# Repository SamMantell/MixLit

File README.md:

# MixLit - Work in Progress

The MixLit is a small sound desk that can control app volumes on a Windows PC. It uses an arduino nano as the controller and talks to our software over USB serial.

The case can be 3D printed and both STEP and STL files are provided

The PCB was designed in KiCAD and we used PCB Way to get them manafactured

Software is a Flutter application.

This repo contains firmware, software and hardware.

# Images
Image of the device:

PCB:

Software:

# 📦 Hardware
**» Order the Hardware we used from the links below.**

💡 WS2812B - LIGHTING - https://www.amazon.co.uk/dp/B0CF57NMHN

🎚️ 10K Ohm Slide Potentiometer - https://www.amazon.co.uk/dp/B07PNDLKQQ?psc=1

🎛️ 10K Ohm Rotation Potentiometer - https://www.amazon.co.uk/dp/B07B64MWRF?psc=1

🎮 Arduino Nano - https://www.amazon.co.uk/dp/B0CJHMZZWS

#

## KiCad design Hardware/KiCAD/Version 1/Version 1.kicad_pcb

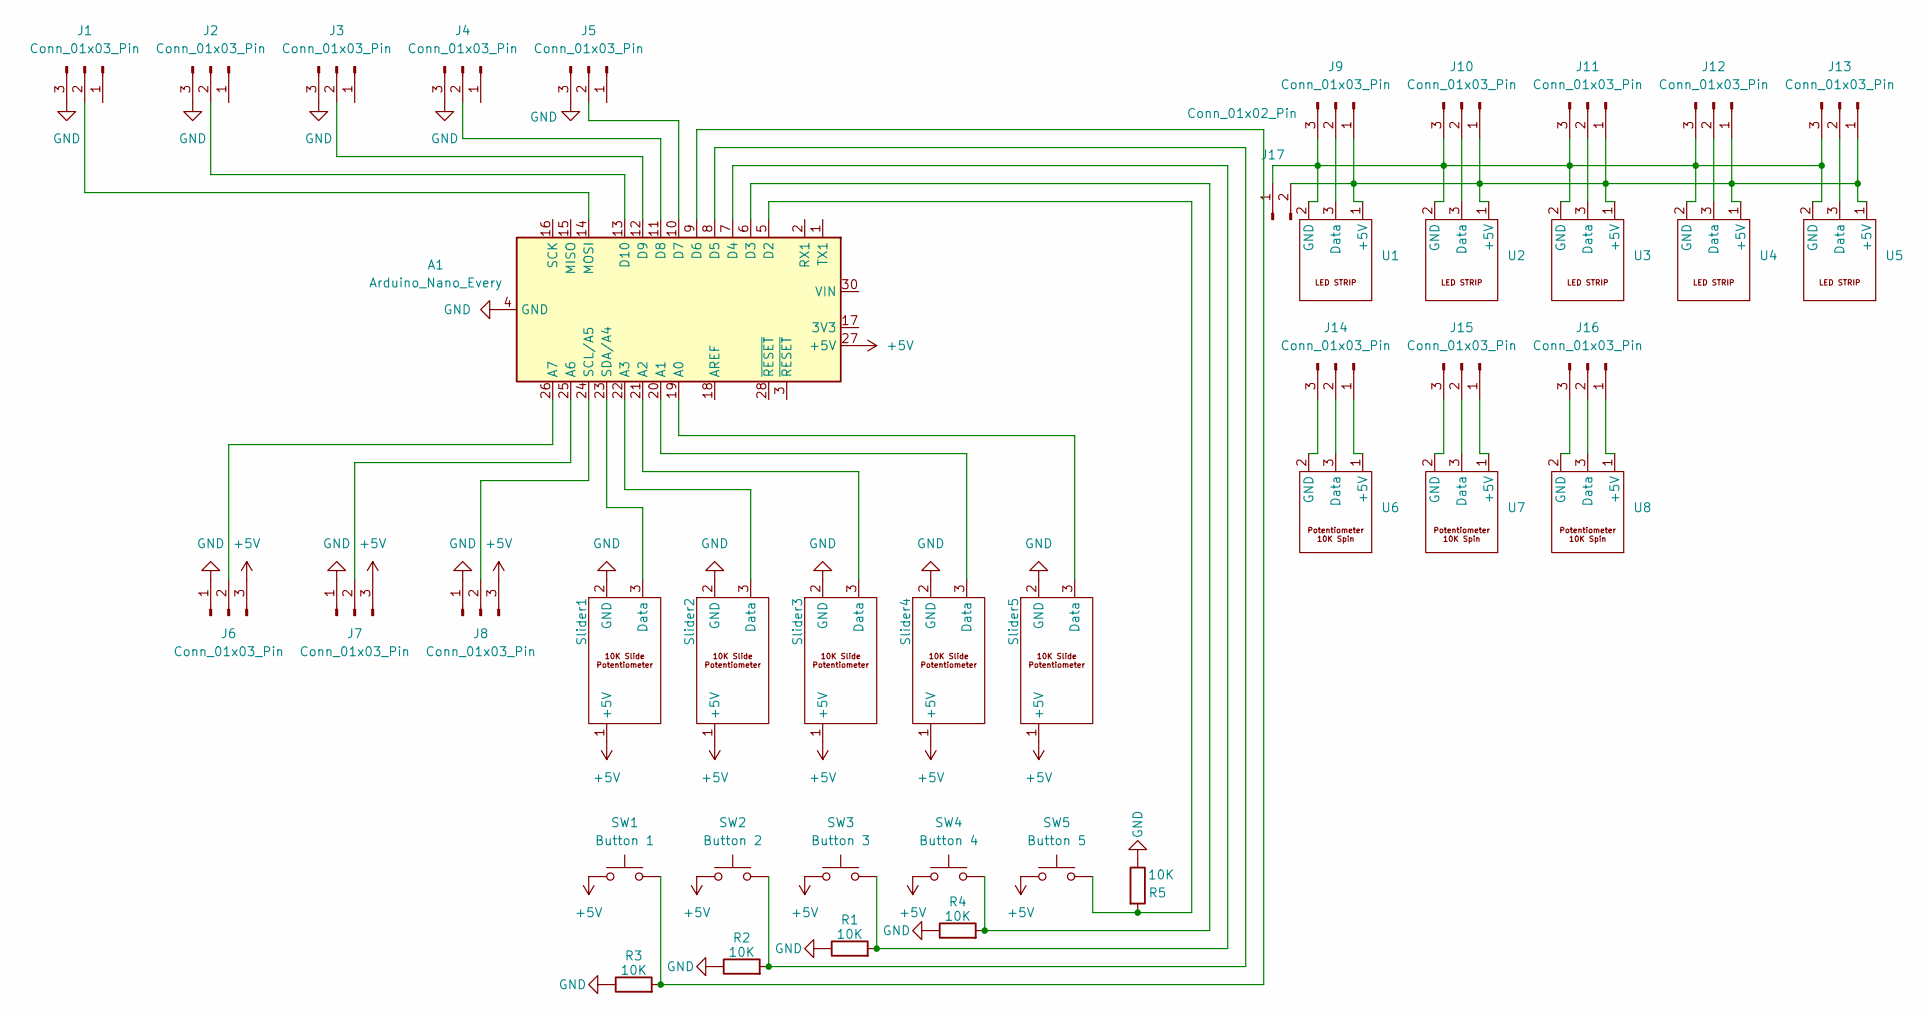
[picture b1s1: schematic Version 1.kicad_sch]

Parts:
A1: Arduino_Nano_Every; Arduino_Nano
J1, J2, J3, J4, J5, J6, J7, J8, J9, J10, J11, J12, J13, J14, J15, J16: Conn_01x03_Pin; PinHeader_1x03_P2.54mm_Vertical
J17: Conn_01x02_Pin; PinHeader_1x02_P2.54mm_Vertical
R1, R2, R3, R4, R5: 10K; R_Axial_DIN0204_L3.6mm_D1.6mm_P7.62mm_Horizontal
SW1: Button 1; SW_Cherry_MX_1.00u_PCB
SW2: Button 2; SW_Cherry_MX_1.00u_PCB
SW3: Button 3; SW_Cherry_MX_1.00u_PCB
SW4: Button 4; SW_Cherry_MX_1.00u_PCB
SW5: Button 5; SW_Cherry_MX_1.00u_PCB
Slider1, Slider2, Slider3, Slider4, Slider5: Custom Slide Potentiometer Double Linear 10K
U1, U2, U3, U4, U5: Custom LED Strip
U6, U7, U8: Custom Spin Potentiometer

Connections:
+5V: A1.27 (+5V), J6.3, J7.3, J8.3, SW1.1, SW2.1, SW3.1, SW4.1, SW5.1, Slider1.1 (+5V), Slider2.1 (+5V), Slider3.1 (+5V), Slider4.1 (+5V), Slider5.1 (+5V)
GND: A1.4 (GND), A1.29 (GND), J1.3, J2.3, J3.3, J4.3, J5.3, J6.1, J7.1, J8.1, R1.1, R2.1, R3.1, R4.1, R5.1, Slider1.2 (GND), Slider2.2 (GND), Slider3.2 (GND), Slider4.2 (GND), Slider5.2 (GND)
unnamed: A1.19 (A0), Slider5.3 (Data)
unnamed: A1.20 (A1), Slider4.3 (Data)
unnamed: A1.21 (A2), Slider3.3 (Data)
unnamed: A1.22 (A3), Slider2.3 (Data)
unnamed: A1.25 (A6), J7.2
unnamed: A1.26 (A7), J6.2
unnamed: A1.5 (D2), R5.2, SW5.2
unnamed: A1.6 (D3), R4.2, SW4.2
unnamed: A1.7 (D4), R1.2, SW3.2
unnamed: A1.8 (D5), R2.2, SW2.2
unnamed: A1.9 (D6), R3.2, SW1.2
unnamed: A1.10 (D7), J5.2
unnamed: A1.11 (D8), J4.2
unnamed: A1.12 (D9), J3.2
unnamed: A1.13 (D10), J2.2
unnamed: A1.14 (MOSI), J1.2
unnamed: A1.24 (SCL/A5), J8.2
unnamed: A1.23 (SDA/A4), Slider1.3 (Data)
unnamed: J9.2, U1.3 (Data)
unnamed: J9.1, J10.1, J11.1, J12.1, J13.1, J17.2, U1.1 (+5V), U2.1 (+5V), U3.1 (+5V), U4.1 (+5V), U5.1 (+5V)
unnamed: J10.2, U2.3 (Data)
unnamed: J9.3, J10.3, J11.3, J12.3, J13.3, J17.1, U1.2 (GND), U2.2 (GND), U3.2 (GND), U4.2 (GND), U5.2 (GND)
unnamed: J11.2, U3.3 (Data)
unnamed: J12.2, U4.3 (Data)
unnamed: J13.2, U5.3 (Data)
unnamed: J14.1, U6.1 (+5V)
unnamed: J14.2, U6.3 (Data)
unnamed: J14.3, U6.2 (GND)
unnamed: J15.1, U7.1 (+5V)
unnamed: J15.2, U7.3 (Data)
unnamed: J15.3, U7.2 (GND)
unnamed: J16.1, U8.1 (+5V)
unnamed: J16.2, U8.3 (Data)
unnamed: J16.3, U8.2 (GND)

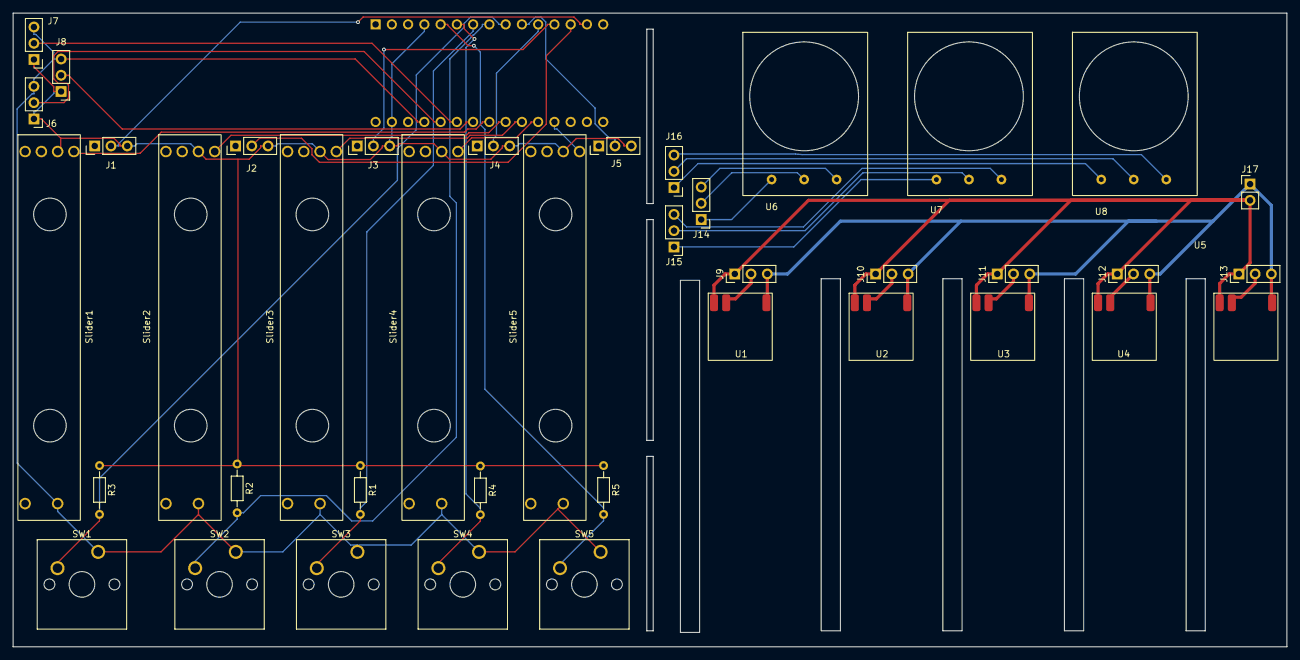
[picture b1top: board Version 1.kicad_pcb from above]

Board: 2 copper layers, 199.0 x 99.0 mm, 41 parts (1 on the bottom side), 36 nets.

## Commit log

2023-08-09 Update MixLit.ino
    Cleaned the code a little
2023-08-10 Optimised + 3D
    Code has been optimised and 3D document added
2023-08-10 Update README.md
    Added Links to Hardware Used
2023-08-10 Update README.md
    new lines are <br />???
2023-08-10 Working LEDS!!!
2023-08-10 bugs FIXED
2023-08-10 Now has Variable at top for deej or not
    woooooo
2023-08-10 test
2023-08-10 software
2023-08-10 clean main repository
2023-08-10 vs gone
2023-08-10 spotify slider test works
2023-08-10 Working-ish app selector for slider 1
2023-08-11 5 workin' slideroos
2023-08-11 quick spring cleaning
2023-08-11 Optimised LEDs
2023-08-12 ui fix
2023-08-14 UI design implementations
2023-08-14 Animation fixes
2023-08-14 attempting to fix sliders mk1
2023-08-14 mkII
2023-08-14 Close button
2023-08-15 might've screwed this optimistic experiment up but hopefully its cool
2023-08-15 some improvments and optimisations?
2023-08-16 Update
    Now 8 Sliders and MIDI usb commented out
2023-08-30 Working for MIDI
    Working now for MIDI VoiceMeter control using 5 sliders
2023-08-30 number wrong lol
2023-08-30 DATA stream lol
2023-09-01 Added some math to calculate values for voice meter
2024-01-05 MixLit V2 Added
    Added new library for the LEDs, now stored in a 2D array, Serial output optimised, some more general optimisations.
2024-01-08 Add Colours to LEDs
    Changed the `setLEDs()` function to make brightness easier and allows for use of colour pallets. Need to create custom colour pallets still.
2024-01-08 Made Cool Blue Colours
    Also some optimisations here and there
2024-01-09 Added Midi
    Can Now Control Voicemeter!!!
2024-01-10 Added a custom ColourPalette
    Added a Custom ColorPalette, do note in future a 16 byte colour palette will be needed to control the master slider while another 32 byte one will be used to control the other 4.
2024-01-11 Implementation of 2 ColorPalettes
    in theory this should add a colour palette for the main slider and one for the others allowing for potential individual addressment of the LEDs over software, wrote this on a coach, code not varified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
2024-01-12 Fixed code from yesterday
    Yeah that code didn't work, hopefully this should, actually verified this one and it should work, can't actually test it, also its not optimised at all atm.
2024-01-25 All White Colour Pallet
    Workin!
2024-01-25 Individually Addressable
    Made it possible to address each led individually with use of 2 arrays, one to control the main slider and the other to control the other 4. Fully Working!
2024-01-27 Remove Serial Communication
    (not using it for now and Arduino will wait for a connection in current config so removed.)
2024-02-01 Removed unnecessary Variables
2024-02-05 Update Non-Colourful
2024-02-07 Update To New Palettes
    No longer CONST!
2024-02-08 Neaten Code
2024-02-08 Update LED type
2024-02-12 Update to New Version
2024-02-12 Fix no `FastLED.show();` lol
2024-02-15 Optimisations
2024-02-15 comment out optimisation checks
2024-02-16 Combined Firmware Together
    Firmware now supports many different modes with a number of variables to enable / disable them.
2024-02-16 Start to read serial data
    tmp, kinda starting to work
2024-02-17 Progress to serial input
    It now takes input!!!
2024-02-17 Bit more progress to serial coms
2024-02-18 Working Serial Communication
    It do be working
2024-02-18 Re-organise code
2024-02-20 Some Documentation
2024-02-25 Remove unnecessary variables
2024-02-26 Few more comments
2024-04-19 Add MixLitLite
2024-05-10 Add first STLs
2024-11-13 add delay between updates
2024-11-13 voicemeter mode
2024-11-13 string build change
2024-11-14 decrease chance of noise
2024-11-14 2024 :)
2024-11-15 never back down never what 🗣️
2024-11-16 herm
2024-12-04 add blender referance
2024-12-04 pcb start
2024-12-05 some more pcbing
2024-12-06 pcb progress
2024-12-09 some more KiCAD Stuff
2024-12-11 more kicad stuff
2024-12-11 ready to order maybe
2024-12-11 to be ordererd
2024-12-20 some changes
2024-12-22 push...
2024-12-22 test one
2024-12-22 This works! Sliders and Pots only though
2024-12-22 Fully working except buttons
2024-12-22 🗣️🔥init 🍵🫖
2024-12-22 🔘🔳 button support maybe
2024-12-23 ✨feat: easily callable dialog for warning messages 🛠️fix: hang on failure of device detection/com-port-open (works with/without device connection now 🎉)
2024-12-23 add a wait for software connection
2024-12-23 ✨feat: device connection / disconnection listeners + toast notification
2024-12-23 fix brightness
2024-12-24 🛠️fix: device connect / disconnection listener
2024-12-24 fix leds going to zero
2024-12-24 ✨feat: mixlit device establishment via COM port call/response scanning ⚠️issues: non-immediate connection, last com port not stored, takes ages to find device, values aren't restored from device on i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
2024-12-24 🔥opt: sped up device recognition process
2024-12-24 🛠️fix: device + app volumes can now co-exist
2024-12-24 🛠️fix: weird ass muting bug
2024-12-28 🛠️fix: device scanning & detection
2025-01-02 add CLion version
2025-02-07 ermmmmm
2025-02-07 create v2
2025-02-07 add case v2
2025-02-16 add spin dial cover
2025-02-23 🛠️fix: basically everything
2025-02-23 ✨﻿ firmware now sends data after connection
    committing firmware to software
2025-02-24 optimise and add loading animation
2025-02-27 remove Clion Version
2025-02-27 remove clio metadata
2025-02-27 ✨ add loading animation
2025-02-27 Revert "Delete pubspec.lock"
    This reverts commit d0521a3f248a7181f752d74ffe61f75d296f536d.
2025-02-27 🔨Optimisations
2025-02-27 add assets
2025-05-09 🛠️ load last saved
2025-05-09 🛠️ Delay fix (fixes laggy result in software) - 50ms -> 10ms
2025-05-09 firmware
2025-05-09 🛠️ Windows volume lags when adjusting too often
2025-05-09 🛠️ Firmware: Reduced noise 🛠️ Prevented app being constantly assigned when volume adjustments are being made
2025-05-09 noise fixes
2025-05-10 ✨ Mute buttons
2025-05-10 🛠️ Mute buttons more responsive
2025-05-10 🧶Refactor: organised assets
2025-05-10 ✨ Basic UI Redesign
2025-05-10 ✨ feat: Saving to config for state restoration 🚢 prgrs: Device LED control from software 🧹 chore: updated logo and theme
2025-05-10 🛠️ Fix: inconsistent design, consistent font, better text clarity/translations
2025-05-10 🔧 tweak: updated app icon
2025-05-10 🛠️ fix: used local directory of application for config instead of documents 🧶ref: changed mixlit.yml to data.yml
2025-05-10 ✨ feat: (Auto) Updater ✨ feat: installer executable using inno 📂 file: added icons, and other assets required for this release
2025-05-10 🧹chore: organise graphic assets
2025-05-10 ✨ feat: Minimise to system tray
2025-05-10 🧹chore: versioning oopsie lol
2025-05-15 🧶 Refactor: finals/consts added where necessary
2025-05-15 ✨ feat: rate limiting for performance, caching 🧶 refactor: icon colour extraction, only using state when necessary 🔧 tweak: edited main.cpp for window size & title 🛠️ fix: firmware type errors
2025-05-15 colour change over serial
2025-05-15 🗣️init
2025-05-15 psuh
2025-05-16 ✨feat: better disconnection handling (no keepalive needed) 🛠️fix: prevented system apps (explorer.exe) without readable file path from causing slider assignment menu breaking ❌rm: temporarily removed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
2025-05-25 beginning to work with classes
2025-05-25 serial reader working with 1 command
2025-05-25 pre datasetled re-write
2025-05-25 working with new serial reader :)
2025-05-25 🔧updated baud rate to match firmware
2025-05-25 organised (almost)
2025-05-26 new code organised
2025-06-08 add buttons to firmware
2025-06-13 ✨ Launch (minimised) on startup ✨ Draggable window ✨ Slight app assigner menu UI update 🔧 Already assigned apps are not listed in app assigner 🛠️ Fixed device volume being muted on start
2025-06-26 support 2 potentiometers and colour gradients
2025-07-03 🛠️ fix #15: config now stored in appdata
2025-07-03 🛠️ fix: connection status indicator overflow (when disconnected)
2025-07-03 improve serial connection
2025-07-03 make only 2 dials for starts of dial integration (left one broke lol)
2025-07-03 ✨feat: dynamic audio session management & app caching (fixes #14)
2025-07-03 🛠️fix #18: show window on manual open (and minimise on startup)
2025-07-03 send all slider values even if 0
2025-07-03 LED updates are now instant
2025-07-07 ✨feat #20: dial support ✨feat #22: settings menu added 🛠️fix #23: mute buttons work again 🛠️fix #19: assigned apps no longer muted on launch
2025-07-07 🧶update version
2025-07-14 Feature - App Grouping
2025-07-17 STM32 moment
2025-10-11 ✨feat #16 - App Grouping ✨feat - Active application support ✨⚡feat+perf: API-based volume adjustment via Windows Service ❌rm: direct audio control
2025-10-30 🛠️ pre-tweaks
2025-10-31 ✨ feat: dynamic/live-updating app list (fixes #26) 🛠️ fix: app re-discovery works (and sets volume upon rediscovery if appropriate slider adjusted) 🛠️ fix #25: hardware values are properly restored u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
2025-11-23 ✨ added session caching 🛠️ fixed memory leak issues
2025-12-21 ✨ added integrations/plugins
2025-12-22 add !
2026-04-05 ✨ ----- VERSION 2.0.0 ----- ⚡ Moved all serial code to be handled by service instead 🛠️ Fixed new apps added to groups not instantly applying once saving the group changes (#28) ✨ Noise reduction alg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
